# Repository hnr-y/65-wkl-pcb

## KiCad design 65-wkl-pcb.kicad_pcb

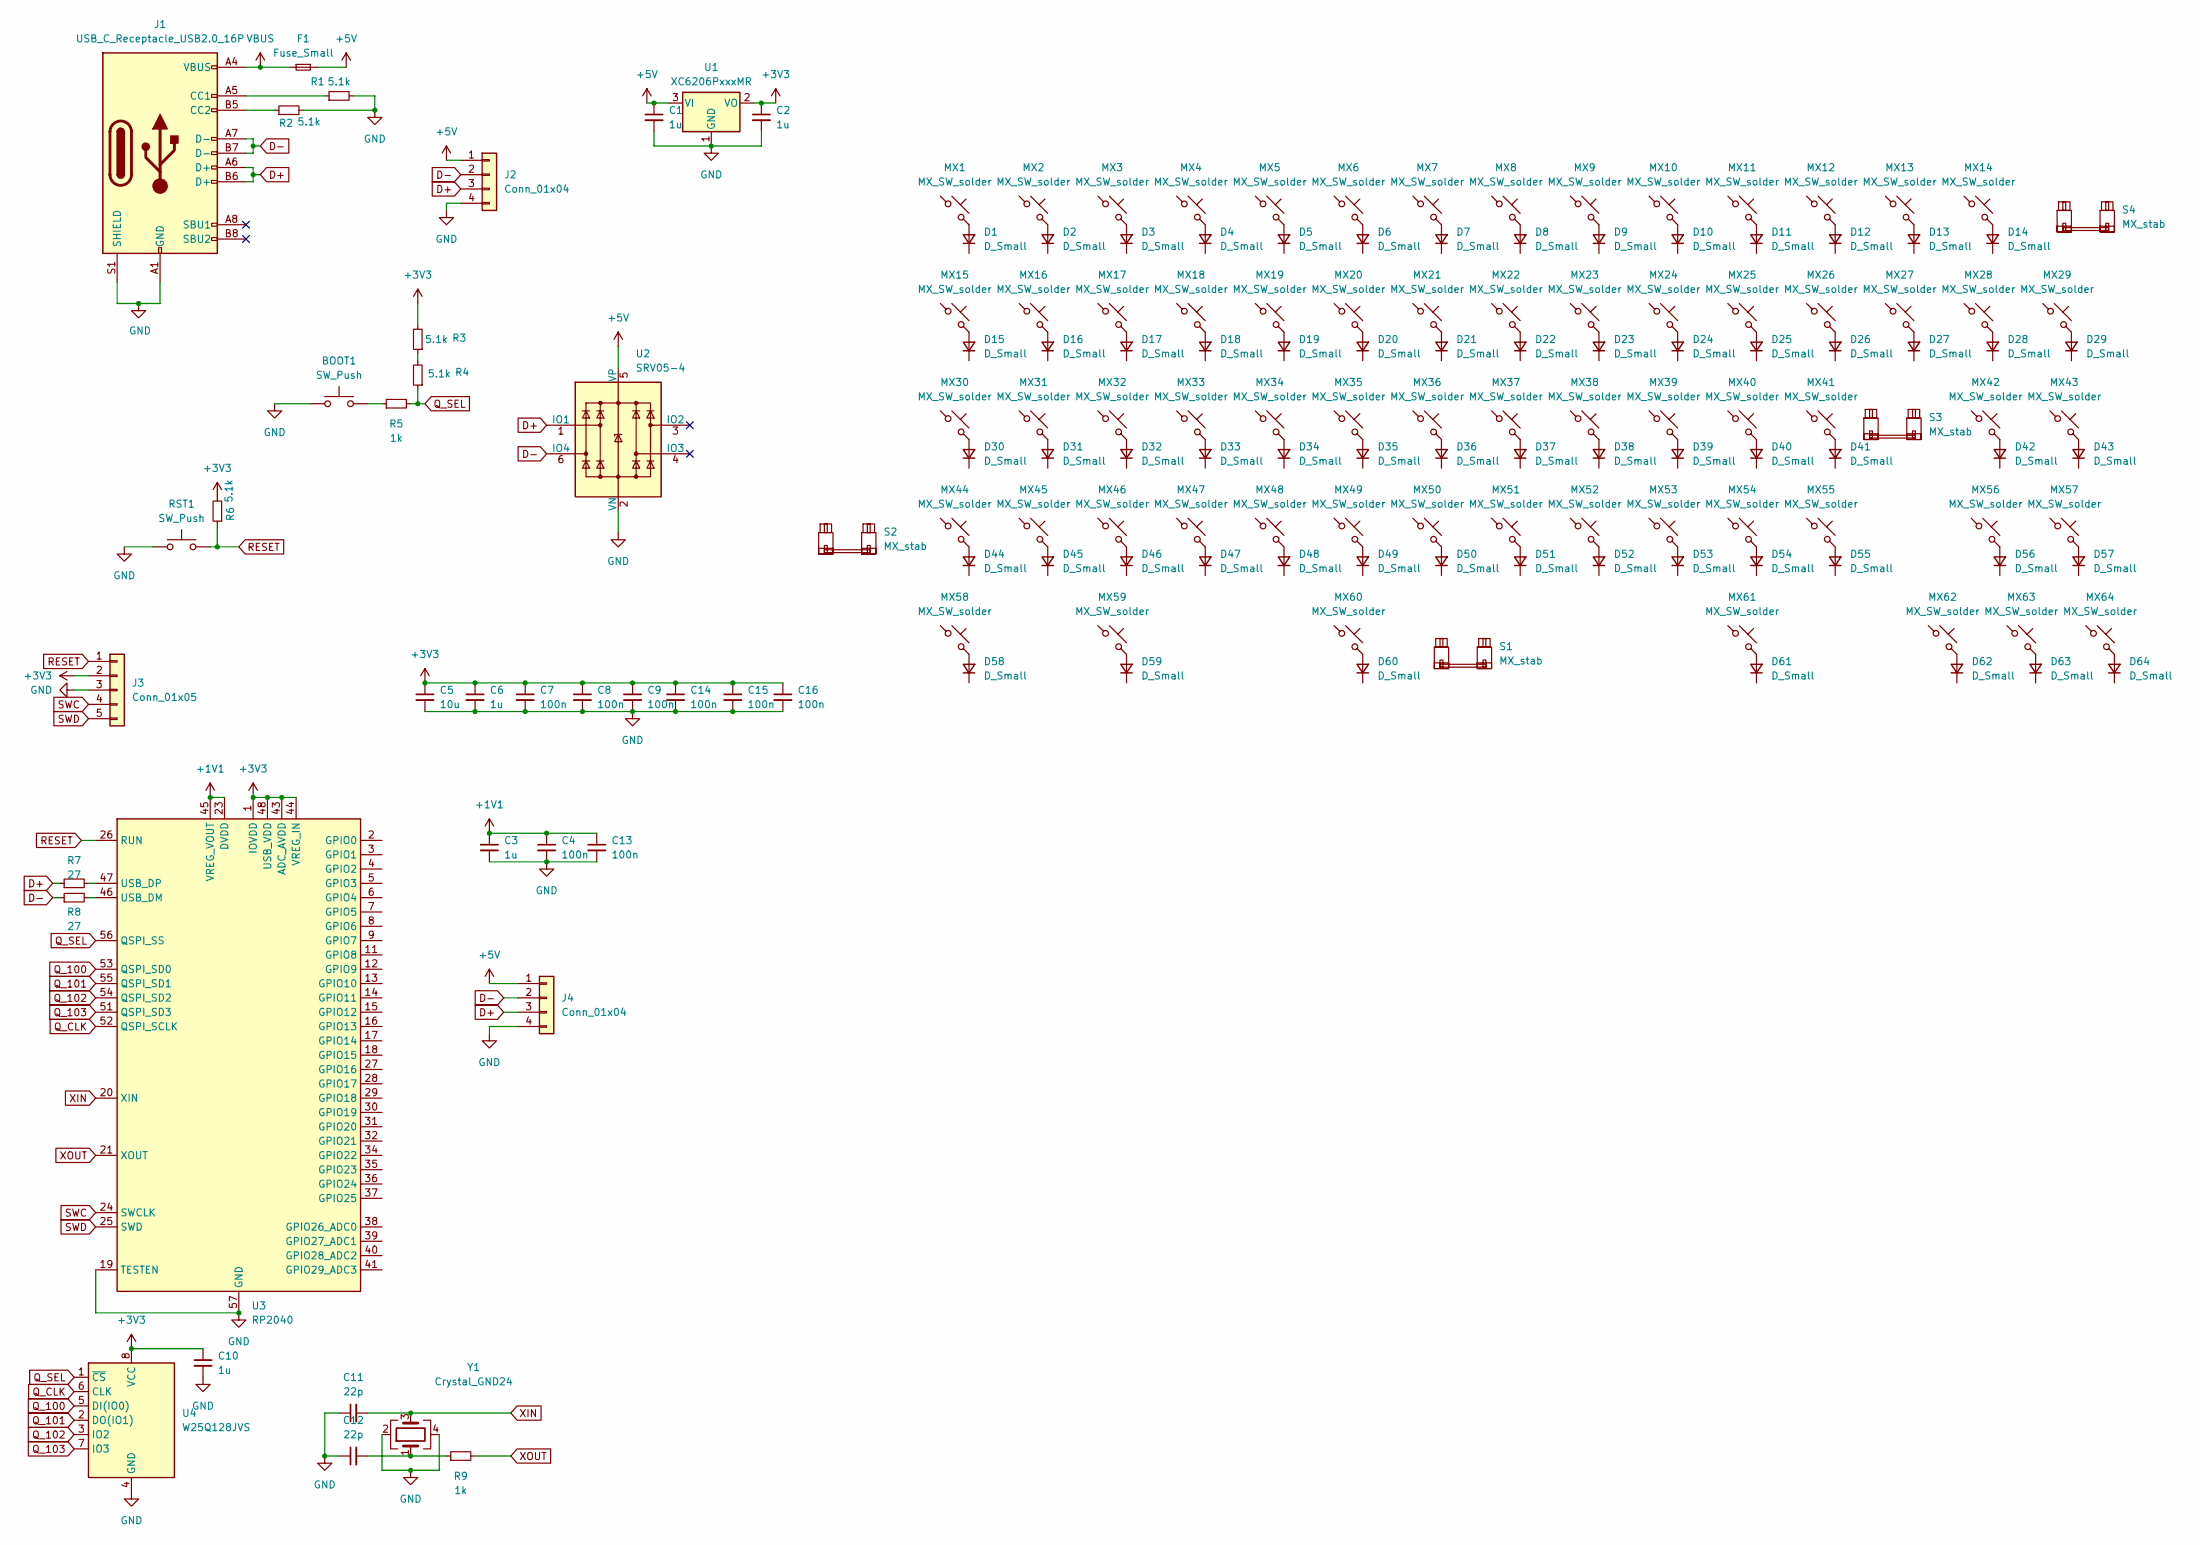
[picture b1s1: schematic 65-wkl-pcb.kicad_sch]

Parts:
BOOT1: SW_Push; SW_SPST_TL3342
C1, C2, C3, C6, C10: 1u; C_0402_1005Metric
C4, C7, C8, C9, C13, C14, C15, C16: 100n; C_0402_1005Metric
C5: 10u; C_0603_1608Metric
C11, C12: 22p; C_0402_1005Metric
D1, D2, D3, D4, D5, D6, D7, D8, D9, D10, D11, D12, D13, D14, D15, D16, D17, D18, D19, D20, D21, D22, D23, D24, D25, D26, D27, D28, D29, D30, D31, D32, D33, D34, D35, D36, D37, D38, D39, D40, D41, D42, D43, D44, D45, D46, D47, D48, D49, D50, D51, D52, D53, D54, D55, D56, D57, D58, D59, D60, D61, D62, D63, D64: D_Small; D_SOD-123
F1: Fuse_Small; Fuse_1206_3216Metric
J1: USB_C_Receptacle_USB2.0_16P; USB_C_Receptacle_HRO_TYPE-C-31-M-12
J2, J4: Conn_01x04; JST_PH_S4B-PH-K_1x04_P2.00mm_Horizontal
J3: Conn_01x05; PinSocket_1x05_P2.54mm_Vertical
MX1, MX2, MX3, MX4, MX5, MX6, MX7, MX8, MX9, MX10, MX11, MX12, MX13, MX14, MX16, MX17, MX18, MX19, MX20, MX21, MX22, MX23, MX24, MX25, MX26, MX27, MX28, MX29, MX31, MX32, MX33, MX34, MX35, MX36, MX37, MX38, MX39, MX40, MX41, MX42, MX43, MX44, MX45, MX46, MX47, MX48, MX49, MX50, MX51, MX52, MX53, MX54, MX56, MX57, MX60, MX62, MX63, MX64: MX_SW_solder; SW_MX_1u
MX15, MX58, MX59, MX61: MX_SW_solder; SW_MX_1.5u
MX30, MX55: MX_SW_solder; SW_MX_1.75u
R1, R2, R3, R4, R6: 5.1k; R_0402_1005Metric
R5, R9: 1k; R_0402_1005Metric
R7, R8: 27; R_0402_1005Metric
RST1: SW_Push; SW_SPST_TL3342
S1: MX_stab; STAB_MX_P_6.25u
S2, S3: MX_stab; STAB_MX_P_2.25u
S4: MX_stab; STAB_MX_P_2u
U1: XC6206PxxxMR; SOT-23-3
U2: SRV05-4; SOT-23-6-routable
U3: RP2040; QFN-56-1EP_7x7mm_P0.4mm_EP3.2x3.2mm
U4: W25Q128JVS; SOIC-8_5.23x5.23mm_P1.27mm
Y1: Crystal_GND24; Crystal_SMD_3225-4Pin_3.2x2.5mm

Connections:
+1V1: C3.1, C4.1, C13.1, U3.23 (DVDD), U3.45 (VREG_VOUT), U3.50 (DVDD)
+3V3: C2.1, C5.1, C6.1, C7.1, C8.1, C9.1, C10.1, C14.1, C15.1, C16.1, J3.2, R3.2, R6.2, U1.2 (VO), U3.1 (IOVDD), U3.10 (IOVDD), U3.22 (IOVDD), U3.33 (IOVDD), U3.42 (IOVDD), U3.43 (ADC_AVDD), U3.44 (VREG_IN), U3.48 (USB_VDD), U3.49 (IOVDD), U4.8 (VCC)
+5V: C1.1, F1.2, J2.1, J4.1, U1.3 (VI), U2.5 (VP)
D+: J1.A6 (D+), J1.B6 (D+), J2.3, J4.3, R7.1, U2.1 (IO1)
D-: J1.A7 (D-), J1.B7 (D-), J2.2, J4.2, R8.1, U2.6 (IO4)
GND: BOOT1.1, C1.2, C2.2, C3.2, C4.2, C5.2, C6.2, C7.2, C8.2, C9.2, C10.2, C11.1, C12.1, C13.2, C14.2, C15.2, C16.2, J1.A1 (GND), J1.A12 (GND), J1.B1 (GND), J1.B12 (GND), J1.S1 (SHIELD), J2.4, J3.3, J4.4, R1.2, R2.2, RST1.1, U1.1 (GND), U2.2 (VN), U3.19 (TESTEN), U3.57 (GND), U4.4 (GND), Y1.2, Y1.4
unnamed: BOOT1.2, R5.1
unnamed: C12.2, R9.1, Y1.1
unnamed: D1.2 (A), MX1.2
unnamed: D2.2 (A), MX2.2
unnamed: D3.2 (A), MX3.2
unnamed: D4.2 (A), MX4.2
unnamed: D5.2 (A), MX5.2
unnamed: D6.2 (A), MX6.2
unnamed: D7.2 (A), MX7.2
unnamed: D8.2 (A), MX8.2
unnamed: D9.2 (A), MX9.2
unnamed: D10.2 (A), MX10.2
unnamed: D11.2 (A), MX11.2
unnamed: D12.2 (A), MX12.2
unnamed: D13.2 (A), MX13.2
unnamed: D14.2 (A), MX14.2
unnamed: D15.2 (A), MX15.2
unnamed: D16.2 (A), MX16.2
unnamed: D17.2 (A), MX17.2
unnamed: D18.2 (A), MX18.2
unnamed: D19.2 (A), MX19.2
unnamed: D20.2 (A), MX20.2
unnamed: D21.2 (A), MX21.2
unnamed: D22.2 (A), MX22.2
unnamed: D23.2 (A), MX23.2
unnamed: D24.2 (A), MX24.2
unnamed: D25.2 (A), MX25.2
unnamed: D26.2 (A), MX26.2
unnamed: D27.2 (A), MX27.2
unnamed: D28.2 (A), MX28.2
unnamed: D29.2 (A), MX29.2
unnamed: D30.2 (A), MX30.2
unnamed: D31.2 (A), MX31.2
unnamed: D32.2 (A), MX32.2
unnamed: D33.2 (A), MX33.2
unnamed: D34.2 (A), MX34.2
unnamed: D35.2 (A), MX35.2
unnamed: D36.2 (A), MX36.2
unnamed: D37.2 (A), MX37.2
unnamed: D38.2 (A), MX38.2
unnamed: D39.2 (A), MX39.2
unnamed: D40.2 (A), MX40.2
unnamed: D41.2 (A), MX41.2
unnamed: D42.2 (A), MX42.2
unnamed: D43.2 (A), MX43.2
unnamed: D44.2 (A), MX44.2
unnamed: D45.2 (A), MX45.2
unnamed: D46.2 (A), MX46.2
unnamed: D47.2 (A), MX47.2
unnamed: D48.2 (A), MX48.2
unnamed: D49.2 (A), MX49.2
unnamed: D50.2 (A), MX50.2
unnamed: D51.2 (A), MX51.2
unnamed: D52.2 (A), MX52.2
unnamed: D53.2 (A), MX53.2
unnamed: D54.2 (A), MX54.2
unnamed: D55.2 (A), MX55.2
unnamed: D56.2 (A), MX56.2
unnamed: D57.2 (A), MX57.2
unnamed: D58.2 (A), MX58.2
unnamed: D59.2 (A), MX59.2
unnamed: D60.2 (A), MX60.2
unnamed: D61.2 (A), MX61.2
unnamed: D62.2 (A), MX62.2
unnamed: D63.2 (A), MX63.2
unnamed: D64.2 (A), MX64.2
unnamed: J1.A5 (CC1), R1.1
unnamed: J1.B5 (CC2), R2.1
unnamed: R3.1, R4.2
unnamed: R8.2, U3.46 (USB_DM)
unnamed: R7.2, U3.47 (USB_DP)
Q_100: U3.53 (QSPI_SD0), U4.5 (DI(IO0))
Q_101: U3.55 (QSPI_SD1), U4.2 (DO(IO1))
Q_102: U3.54 (QSPI_SD2), U4.3 (IO2)
Q_103: U3.51 (QSPI_SD3), U4.7 (IO3)
Q_CLK: U3.52 (QSPI_SCLK), U4.6 (CLK)
Q_SEL: R4.1, R5.2, U3.56 (QSPI_SS), U4.1 (~CS)
RESET: J3.1, R6.1, RST1.2, U3.26 (RUN)
SWC: J3.4, U3.24 (SWCLK)
SWD: J3.5, U3.25 (SWD)
VBUS: F1.1, J1.A4 (VBUS), J1.A9 (VBUS), J1.B4 (VBUS), J1.B9 (VBUS)
XIN: C11.2, U3.20 (XIN), Y1.3
XOUT: R9.2, U3.21 (XOUT)

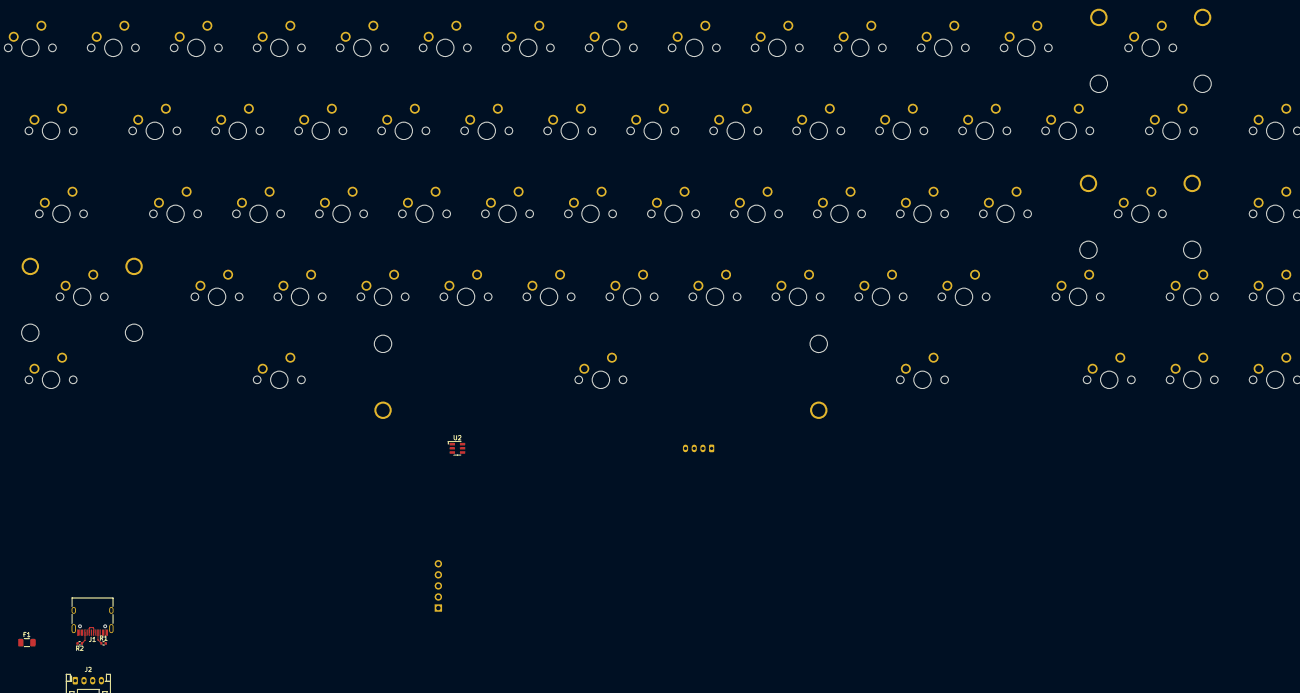
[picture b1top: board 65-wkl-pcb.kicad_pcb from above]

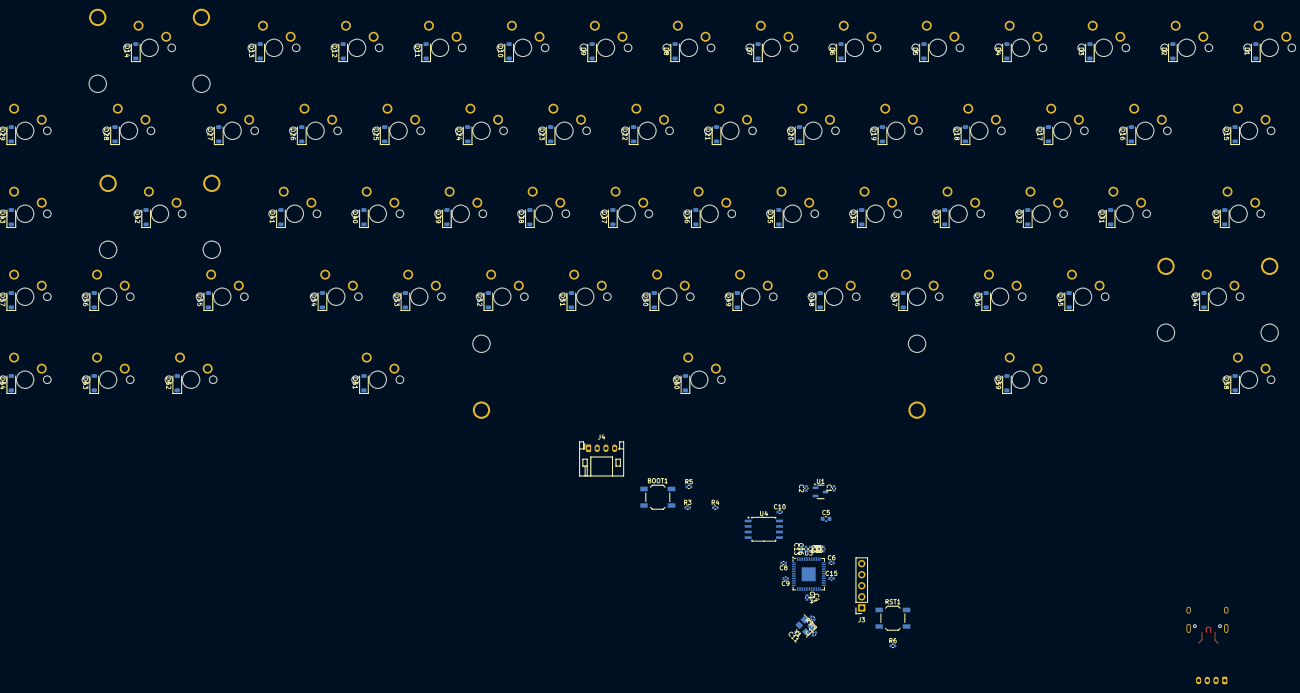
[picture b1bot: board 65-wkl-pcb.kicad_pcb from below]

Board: 2 copper layers, 169 parts (95 on the bottom side), 89 nets.

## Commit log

2024-08-21 updating
2024-08-22 daughterboard
